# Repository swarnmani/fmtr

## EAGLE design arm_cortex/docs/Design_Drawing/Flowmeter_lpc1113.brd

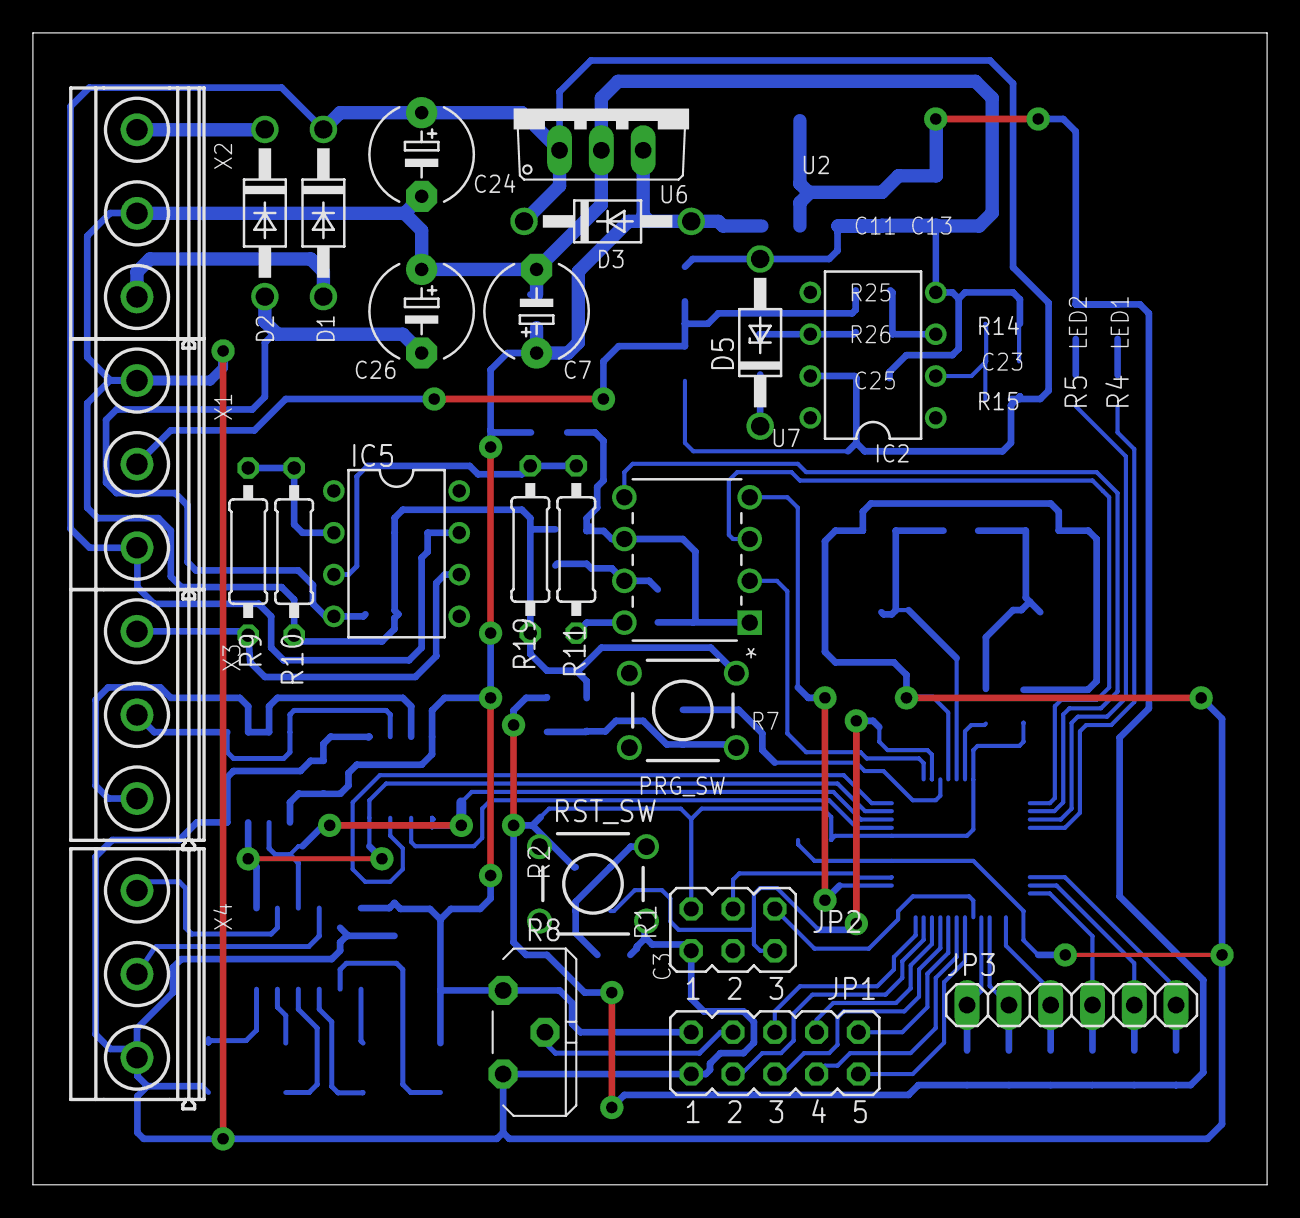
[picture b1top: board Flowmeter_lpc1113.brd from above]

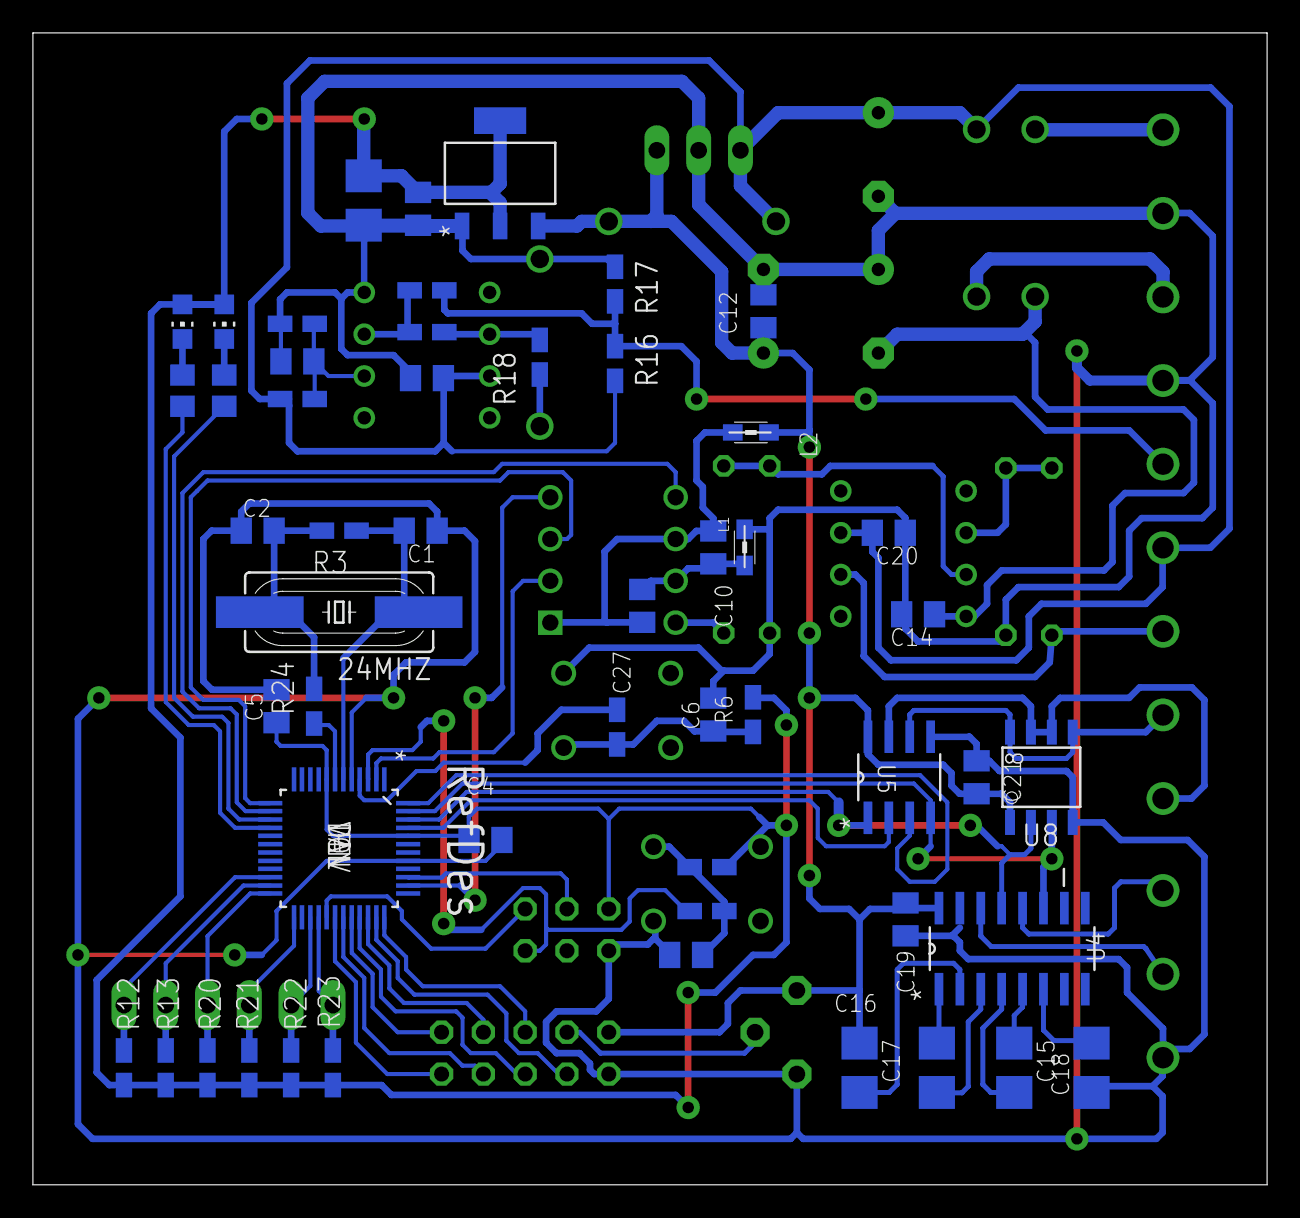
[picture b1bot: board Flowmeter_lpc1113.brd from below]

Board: 2 copper layers, 75.0 x 70.0 mm, 77 parts (52 on the bottom side), 63 nets.

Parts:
24MHZ: 12MHz; HC49UP
C1, C2, C3, C6: 18p; C0805K
C4, C5, C10, C11, C12, C14, C19, C20, C21, C23, C25, C27: 100n; C0805K
C7: 10uF; E5-6
C13: 10µ; CT3528
C15, C16, C17, C18: CT3528
C24, C26: 100uF/60V; E5-6
D1, D2, D3: 1N4004; DO41-10
D5: 3.3V; DO41Z10
IC2, IC5: OP07CN; DIL08
JP1: JP5Q
JP2: JP3Q
JP3: 1X06
L1, L2: WURTH ELEKTRONIK - 742792095; 0805
LED1, LED2: CHIP-LED0805
PRG_SW: TACTILE-PTH
R1, R2, R6, R7, R12, R13, R14, R15, R16, R17, R18, R20, R21, R22, R23, R25: 10k; R0805W
R3: 1M; R0805W
R4, R5: R0805
R8: PT-10S
R9, R10, R11, R19: 10k; 0207/10
R24: 50E; R0805W
R26: 22k; R0805W
RST_SW: TACTILE-PTH
U1: LPC1113FBD48/302,1; QFP50P900X900X160-48N
U2: LD1117S33CTR; SOT230P700X180-4N
U4: MAX232ACSE+; SOIC127P600X175-16N
U5: MAX485CSA+; SOIC127P600X175-8N
U6: 7805TV; TO220V
U7: MCP4921-E/P; DIP254P762X432-8
U8: SP1490; SO-08
X1, X2, X3, X4: MKDSN1,5/3-5,08

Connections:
5V: C7.+, C12.2, C16.-, C19.2, C21.2, D3.A, JP1.2, L2.2, R8.1, U2.3, U4.16, U5.8, U6.3, U8.1
+12V: C20.2, C24.+, C25.1, D1.C, D3.C, IC2.7, IC5.7, R15.1, R16.1, U6.1, X1.1
-12V: C14.1, C26.-, D2.A, IC5.4
/BOOTLOADER: R7.1, U1.4
/RESET: JP2.5, R1.1, U1.3
A: U5.6, U8.5, U8.8, X3.2
B: U5.7, U8.6, U8.7, X3.1
DAC_VOUT: R11.2, U7.8
GND: C1.1, C2.1, C3.2, C4.2, C5.2, C6.2, C7.-, C11.1, C12.1, C13.-, C14.2, C15.+, C19.1, C20.1, C21.1, C23.2, C24.-, C25.2, C26.+, D5.A, IC2.4, JP1.1, JP2.1, L1.1, PRG_SW.2, R8.2, R10.1, R14.2, R17.2, R19.1, RST_SW.4, U1.5, U1.41, U2.1, U4.15, U5.5, U6.2, U8.4, X1.3, X2.2, X4.1
GND1: C10.2, C27.2, L1.2, U7.7
LCD_CONT: JP1.4, R8.3
LCD_D4: JP1.5, U1.33
LCD_D5: JP1.8, U1.34
LCD_D6: JP1.3, U1.35
LCD_D7: JP1.6, U1.36
LCD_EN: JP1.7, U1.31
LCD_R/W: JP1.10, U1.32
LCD_RS: JP1.9, U1.30
LDAC: U1.14, U7.5
LED1: R4.2, U1.16
LED2: R5.2, U1.15
unnamed: LED1.C, R4.1
unnamed: LED2.C, R5.1
unnamed: C3.1, R1.2, R2.1, RST_SW.2
unnamed: C6.1, PRG_SW.4, R6.1, R7.2
unnamed: 24MHZ.2, C2.2, R3.2, R24.2
unnamed: IC2.3, R25.2, R26.1
unnamed: C10.1, C27.1, L2.1, U7.1, U7.6
unnamed: U4.14, X4.2
unnamed: U4.12, X4.3
unnamed: C17.+, U4.1
unnamed: C23.1, IC2.2, R14.1, R15.2
unnamed: IC5.2, R9.1, R10.2
unnamed: IC5.3, R11.1, R19.2
unnamed: D2.C, X2.3
unnamed: D1.A, X2.1
unnamed: C17.-, U4.3
unnamed: C18.+, U4.4
unnamed: C18.-, U4.5
unnamed: C16.+, U4.2
unnamed: C15.-, U4.6
unnamed: IC5.6, R9.2, X3.3
unnamed: IC2.6, R18.2, R26.2
PULSE: D5.C, R18.1
RS485_RX_EN: U1.45, U5.2
RS485_TX_EN: U1.48, U5.3
SENSOR_SIGNAL: R16.2, R17.1, R25.1, X1.2
SPI1_CS: U1.2, U7.2
SPI1_MOSI: U1.38, U7.4
SPI1_SCK: U1.13, U7.3
SWDCLK: JP2.6, U1.29
SWDIO: JP2.4, U1.39
SWITCH0: JP3.1, R23.2, U1.28
SWITCH1: JP3.2, R22.2, U1.27
SWITCH2: JP3.3, R21.2, U1.25
SWITCH3: JP3.4, R20.2, U1.24
SWITCH4: JP3.5, R13.2, U1.23
SWITCH5: JP3.6, R12.2, U1.22
UART_RX: U1.46, U4.13, U5.1, U8.2
UART_TX: U1.47, U4.11, U5.4, U8.3
VCC: C4.1, C5.1, C11.2, C13.+, JP2.2, LED1.A, LED2.A, R2.2, R6.2, R12.1, R13.1, R20.1, R21.1, R22.1, R23.1, U1.8, U1.44, U2.2, U2.4
XTAL_IN: 24MHZ.1, C1.2, R3.1, U1.6
XTAL_OUT: R24.1, U1.7

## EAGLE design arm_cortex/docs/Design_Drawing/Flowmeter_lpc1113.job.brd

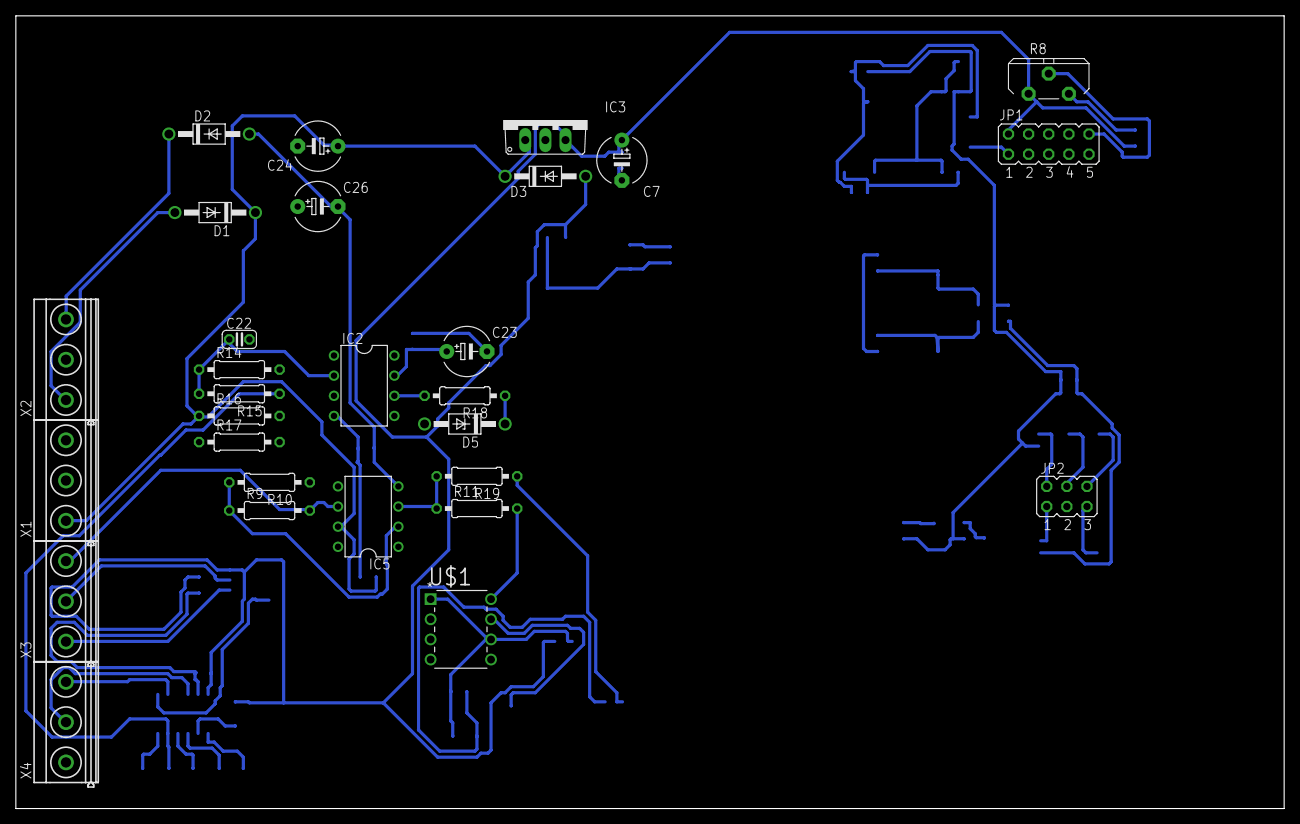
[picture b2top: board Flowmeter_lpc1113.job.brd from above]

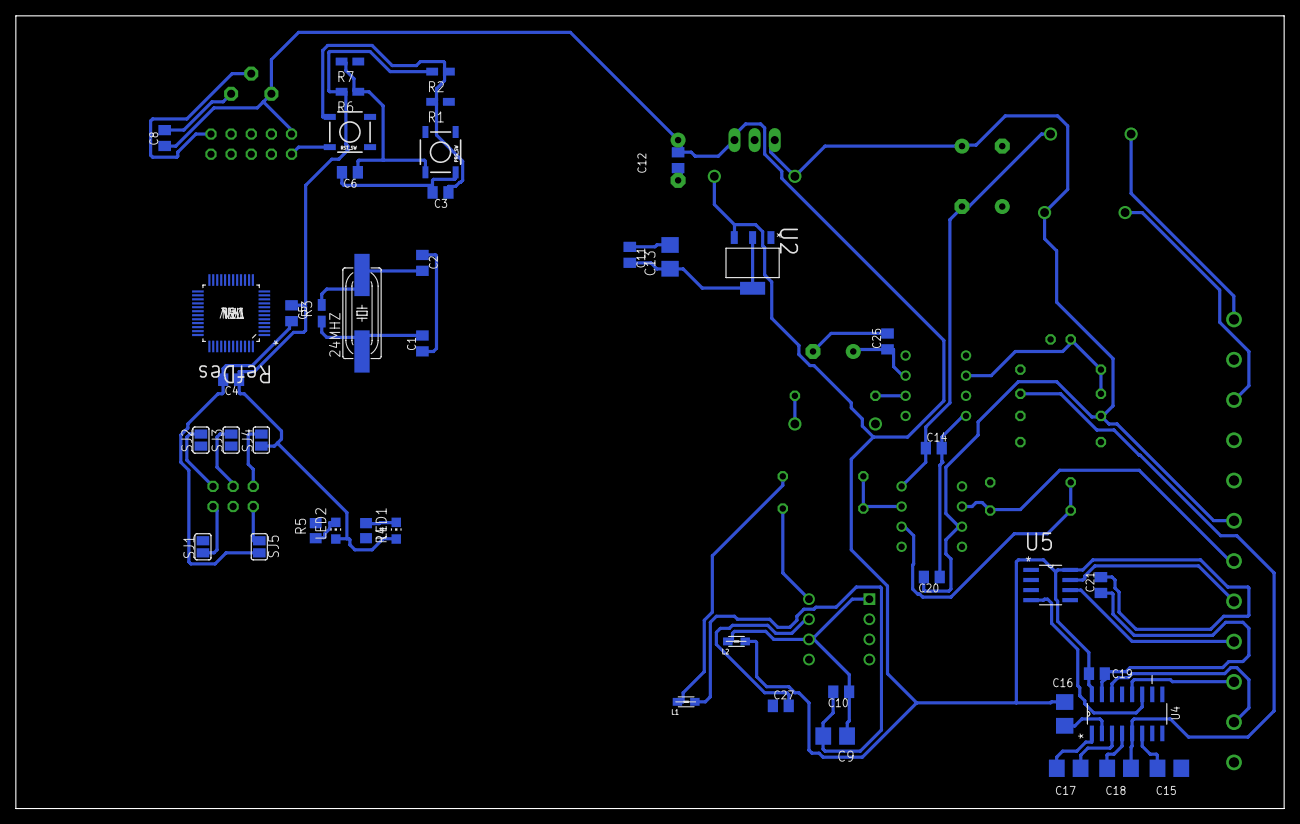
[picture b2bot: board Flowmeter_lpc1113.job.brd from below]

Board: 2 copper layers, 160.0 x 100.0 mm, 74 parts (45 on the bottom side), 63 nets.

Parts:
24MHZ: 12MHz; HC49UP
C1, C2, C3, C6: 18p; C0805K
C4, C5, C8, C10, C11, C12, C14, C19, C20, C21, C25, C27: 100n; C0805K
C7: 10uF; E5-6
C9, C13: 10Âµ; CT3528
C15, C16, C17, C18: CT3528
C22: 100n; C025-024X044
C23, C24, C26: 100uF/60V; E5-6
D1, D2, D3: 1N4004; DO41-10
D5: 3.3V; DO41Z10
IC2, IC5: OP07CN; DIL08
IC3: 7805TV; TO220V
JP1: JP5Q
JP2: JP3Q
L1, L2: WURTH ELEKTRONIK - 742792095; 0805
LED1, LED2: CHIP-LED0805
PRG_SW: TACTILE_SWITCH_SMD
R1, R2, R6, R7: 10k; R0805W
R3: 1M; R0805W
R4, R5: R0805
R8: PT-10S
R9, R10, R11, R14, R15, R16, R17, R18, R19: 10k; 0207/10
RST_SW: TACTILE_SWITCH_SMD
SJ1, SJ2, SJ3, SJ4, SJ5: SJ
U1: LPC1113FBD48/302,1; QFP50P900X900X160-48N
U2: LD1117S33CTR; SOT230P700X180-4N
U4: MAX232ACSE+; SOIC127P600X175-16N
U5: MAX485CSA+; SOIC127P600X175-8N
U$1: MCP4921-E/P; DIP254P762X432-8
X1, X2, X3, X4: MKDSN1,5/3-5,08

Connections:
5V: C7.+, C8.1, C12.2, C16.-, C19.2, C21.2, D3.A, IC3.3, JP1.2, L2.2, R8.1, U2.3, U4.16, U5.8
+12V: C20.2, C24.+, D1.C, D3.C, IC3.1, IC5.7, R16.1, X1.1
-12V: C14.1, C26.-, D2.A, IC5.4
/BOOTLOADER: R7.1, U1.4
/RESET: R1.1, SJ1.2, U1.3
DAC_VOUT: R11.2, U$1.8
GND: C1.1, C2.1, C3.2, C4.2, C5.2, C6.2, C7.-, C8.2, C11.1, C12.1, C13.-, C14.2, C15.+, C19.1, C20.1, C21.1, C22.2, C23.-, C24.-, C25.2, C26.+, D5.A, IC2.4, IC3.2, JP1.1, L1.1, PRG_SW.2, R8.2, R10.1, R14.2, R17.2, R19.1, RST_SW.2, SJ5.2, U1.5, U1.41, U2.1, U4.15, U5.5, X1.3, X2.2, X4.1
GND1: C27.2, U$1.7
LCD_CONT: JP1.10, R8.3
LCD_D4: JP1.3, U1.1
LCD_D5: JP1.4, U1.11
LCD_D6: JP1.5, U1.12
LCD_D7: JP1.6, U1.24
LCD_EN: JP1.7, U1.43
LCD_R/W: JP1.8, U1.37
LCD_RS: JP1.9, U1.36
LDAC: U1.48, U$1.5
LED1: R4.2, U1.21
LED2: R5.2, U1.20
unnamed: LED1.C, R4.1
unnamed: LED2.C, R5.1
unnamed: C9.-, C10.2, L1.2
unnamed: C3.1, R1.2, R2.1, RST_SW.4
unnamed: C6.1, PRG_SW.4, R6.1, R7.2
unnamed: JP2.5, SJ1.1
unnamed: JP2.2, SJ4.2
unnamed: JP2.4, SJ3.2
unnamed: JP2.6, SJ2.2
unnamed: JP2.1, SJ5.1
unnamed: C9.+, C10.1, L2.1, U$1.1, U$1.6
unnamed: U4.14, X4.2
unnamed: U4.12, X4.3
unnamed: C17.+, U4.1
unnamed: C22.1, IC2.2, R14.1, R15.2
unnamed: IC5.2, R9.1, R10.2
unnamed: IC5.3, R11.1, R19.2
unnamed: D2.C, X2.3
unnamed: D1.A, X2.1
unnamed: C23.+, C25.1, IC2.7
unnamed: C17.-, U4.3
unnamed: C18.+, U4.4
unnamed: C18.-, R15.1, U4.5
unnamed: C16.+, U4.2
unnamed: C15.-, U4.6
unnamed: IC5.6, R9.2, X3.3
unnamed: U5.6, X3.1
unnamed: U5.7, X3.2
unnamed: IC2.6, R18.2
unnamed: C11.2, C13.+, U2.2, U2.4
PULSE: D5.C, R18.1
RS485_RX_EN: U1.15, U5.2
RS485_TX_EN: U1.14, U5.3
SENSOR_SIGNAL: IC2.3, R16.2, R17.1, X1.2
SPI1_CS: U1.2, U$1.2
SPI1_MOSI: U1.38, U$1.4
SPI1_SCK: U1.13, U$1.3
SWDCLK: SJ2.1, U1.29
SWDIO: SJ3.1, U1.39
UART_RX: U1.46, U4.13, U5.1
UART_TX: U1.47, U4.11, U5.4
VCC: C4.1, C5.1, LED1.A, LED2.A, R2.2, R6.2, SJ4.1, U1.8, U1.44
XTAL_IN: 24MHZ.1, C1.2, R3.1, U1.6
XTAL_OUT: 24MHZ.2, C2.2, R3.2, U1.7

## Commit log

2014-03-19 initial commit of all documents
2014-03-22 application notes for cortex M0 controllers
2014-03-22 datasheet for vreg and sensor information
2014-04-13 Drawings - to be completed
2014-04-14 added dc switcher components, rs232, rs485
2014-04-20 signal conditioning for Inductive sensor
    Schmitt trigger circuit for Inductive sensor. (12V supply)
2014-04-24 DAC CODE
    DAC and LCD code is updated
2014-04-24 updated Main
    Removed unwanted code
2014-04-24 IO Change details
2014-05-07 UART
    UART code updated
2014-05-13 deleted 12 switching supply deleted 10volt linear regulator supply added +12volt and -12volt linear regulator supply Noninverting amplifier with gain 2 for 0-10volt output 4-20mA output circuit
2014-06-08 removed 4-20mA translation circuit. removed the power 10V supply. added +12V and -12V supply regulator. added bridge rectifier
2014-06-08 removed +12V -12V regulators. added connector for input regulated 12V added lm321 inplace of lm324
2014-06-15 schematic
2014-06-15 New I O change request doc
    Please change the IO s as per the doc
2014-06-15 removed led mosfets
2014-06-15 autorouter
2014-06-18 New Io changes
    Yesterday i forgot to update
2014-06-29 RS485 application note
2014-07-01 Test
2014-07-06 single layer board
2014-07-06 schematic and pcb pdf
2014-07-22 This we will use to dump some non project related docs
